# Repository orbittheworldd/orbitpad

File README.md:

# dylpickle/orbittheworld's Hackpad!
My build for stardance using the "hackpad" macropad tutorial!

I used OnShape as my CAD software. I had very little CAD experience before this project, and I feel that I was able to drastically grow my abilities during this project. I struggled a lot with the proper dimensions, as my extrusions would often end up being the wrong size.

# PCB
Schematic

PCB

This was also my first time using KiCAD to design a PCB. Thankfully, it wasn't too difficult and I will definitely be using it for future projects.

# Case

I will be using heatset inserts and bolts to fasten my case. The heatset inserts will be placed in their designated holes in the top shell.

# Firmware
Firmware was probably the part that I struggled the most with, as I have very little experience programming. Thankfully, KMK was relatively easy to navigate so I was able to write my code without major issues (I'm writing this before I've properly tested the code so hopefully it actually works).

# BOM

| Part          | Quantity      | 
| ------------- |:-------------:|
| Seeed XIAO RP2040   | 1 |
| Cherry MX Switches      | 4 |
| 0.91 inch OLED display | 1 |
| DSA Keycaps | 4 |
| M3x16mm screw | 4 |
| M3x5mx4mm heatset inserts | 4 |
| PCB | 1 |
| Case (3 3d-Printed Parts) | 1 |

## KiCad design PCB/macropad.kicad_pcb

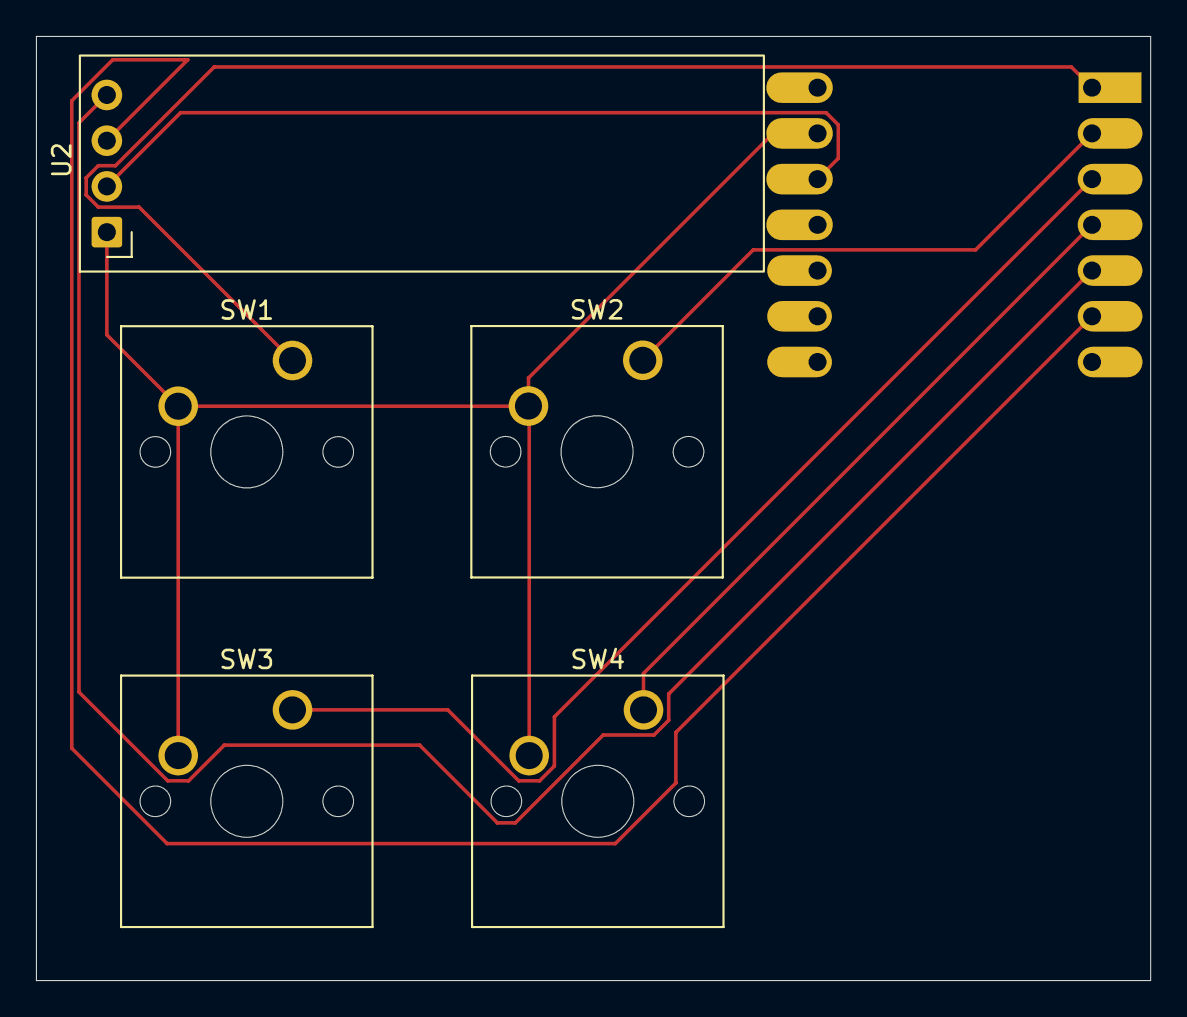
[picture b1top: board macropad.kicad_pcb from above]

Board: 2 copper layers, 61.9 x 52.5 mm, 6 parts (1 on the bottom side), 8 nets.

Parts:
SW1, SW2, SW3, SW4: SW_Push; SW_Cherry_MX_1.00u_PCB
U1: MOUDLE-SEEEDUINO-XIAO; XIAO-Generic-Hybrid-14P-2.54-21X17.8MM
U2: ER_OLEDM0.91_1x-I2C

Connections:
GND: SW1.2, SW2.2, SW3.2, SW4.2, U1.13 (GND), U2.1 (GND)
unnamed: U1.12 (3V3), U2.2 (VCC)
unnamed: SW1.1, U1.1 (PA02_A0_D0)
unnamed: SW2.1, U1.2 (PA4_A1_D1)
unnamed: U1.5 (PA8_A4_D4_SDA), U2.4 (SDA)
unnamed: U1.6 (PA9_A5_D5_SCL), U2.3 (SCL)
unnamed: SW3.1, U1.3 (PA10_A2_D2)
unnamed: SW4.1, U1.4 (PA11_A3_D3)

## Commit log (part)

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2026-06-23 Create hackpad!
2026-06-24 Create full hackpad cad!
2026-06-24 added CAD files
2026-06-24 renamed bottom shell file
2026-06-24 renamed top shell name
2026-06-24 renamed switch plate file name
2026-06-24 adding PCB files
2026-06-24 updating readme!
